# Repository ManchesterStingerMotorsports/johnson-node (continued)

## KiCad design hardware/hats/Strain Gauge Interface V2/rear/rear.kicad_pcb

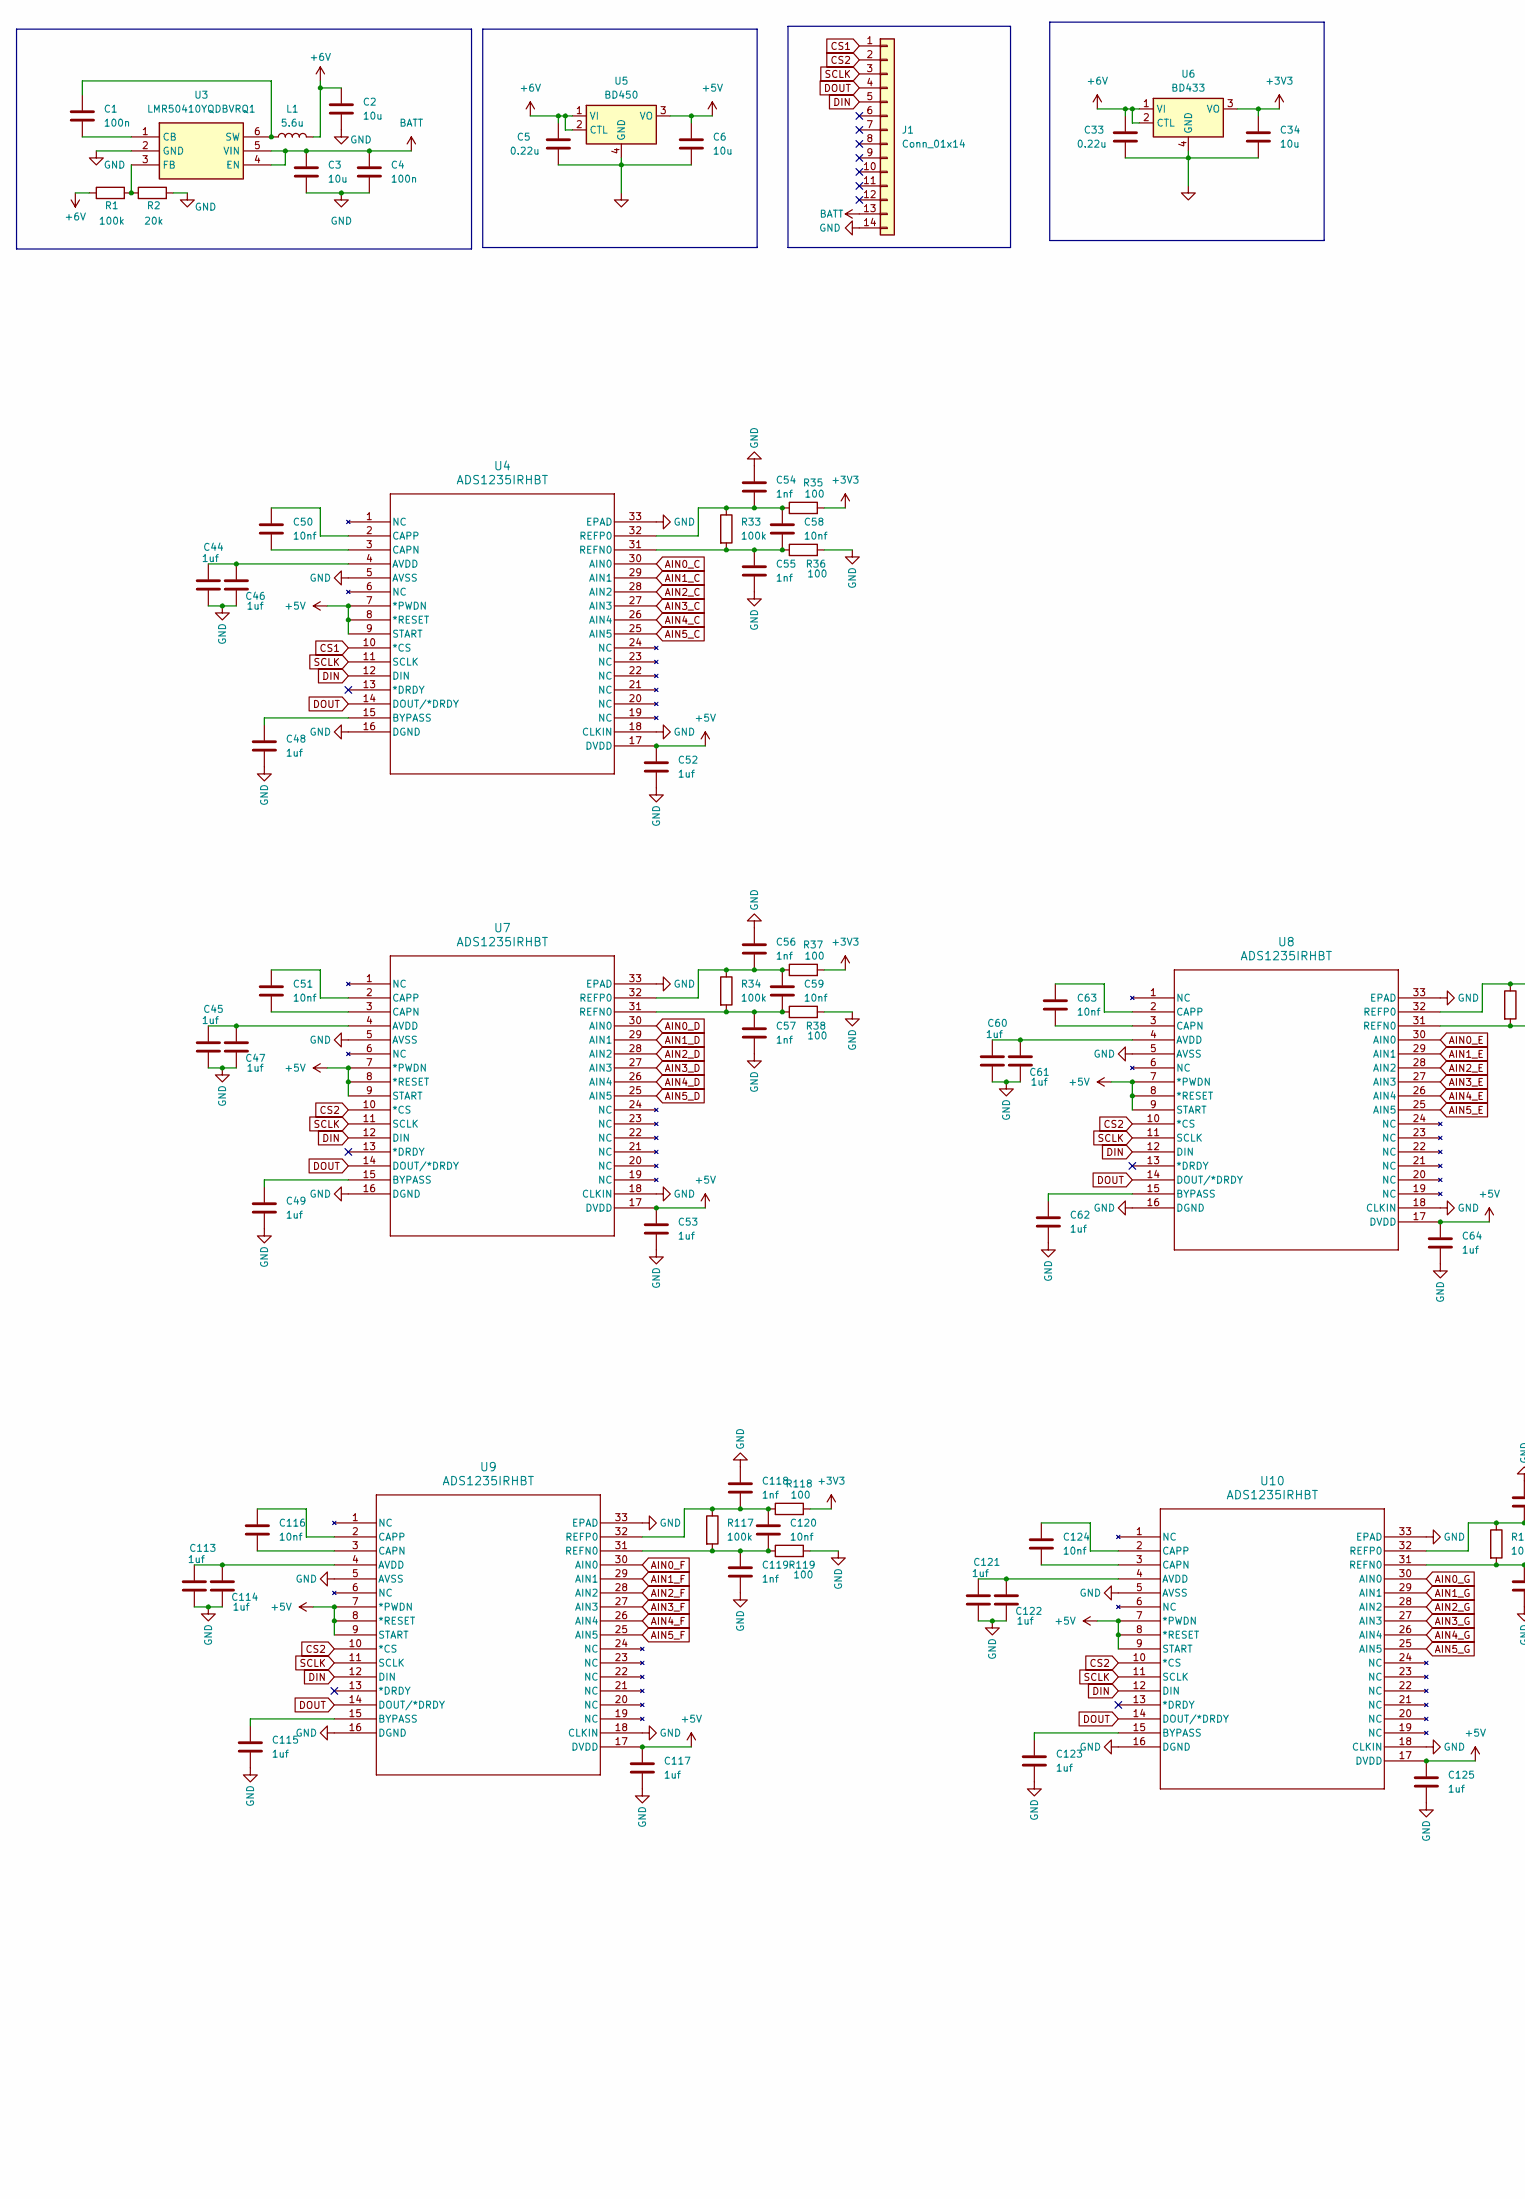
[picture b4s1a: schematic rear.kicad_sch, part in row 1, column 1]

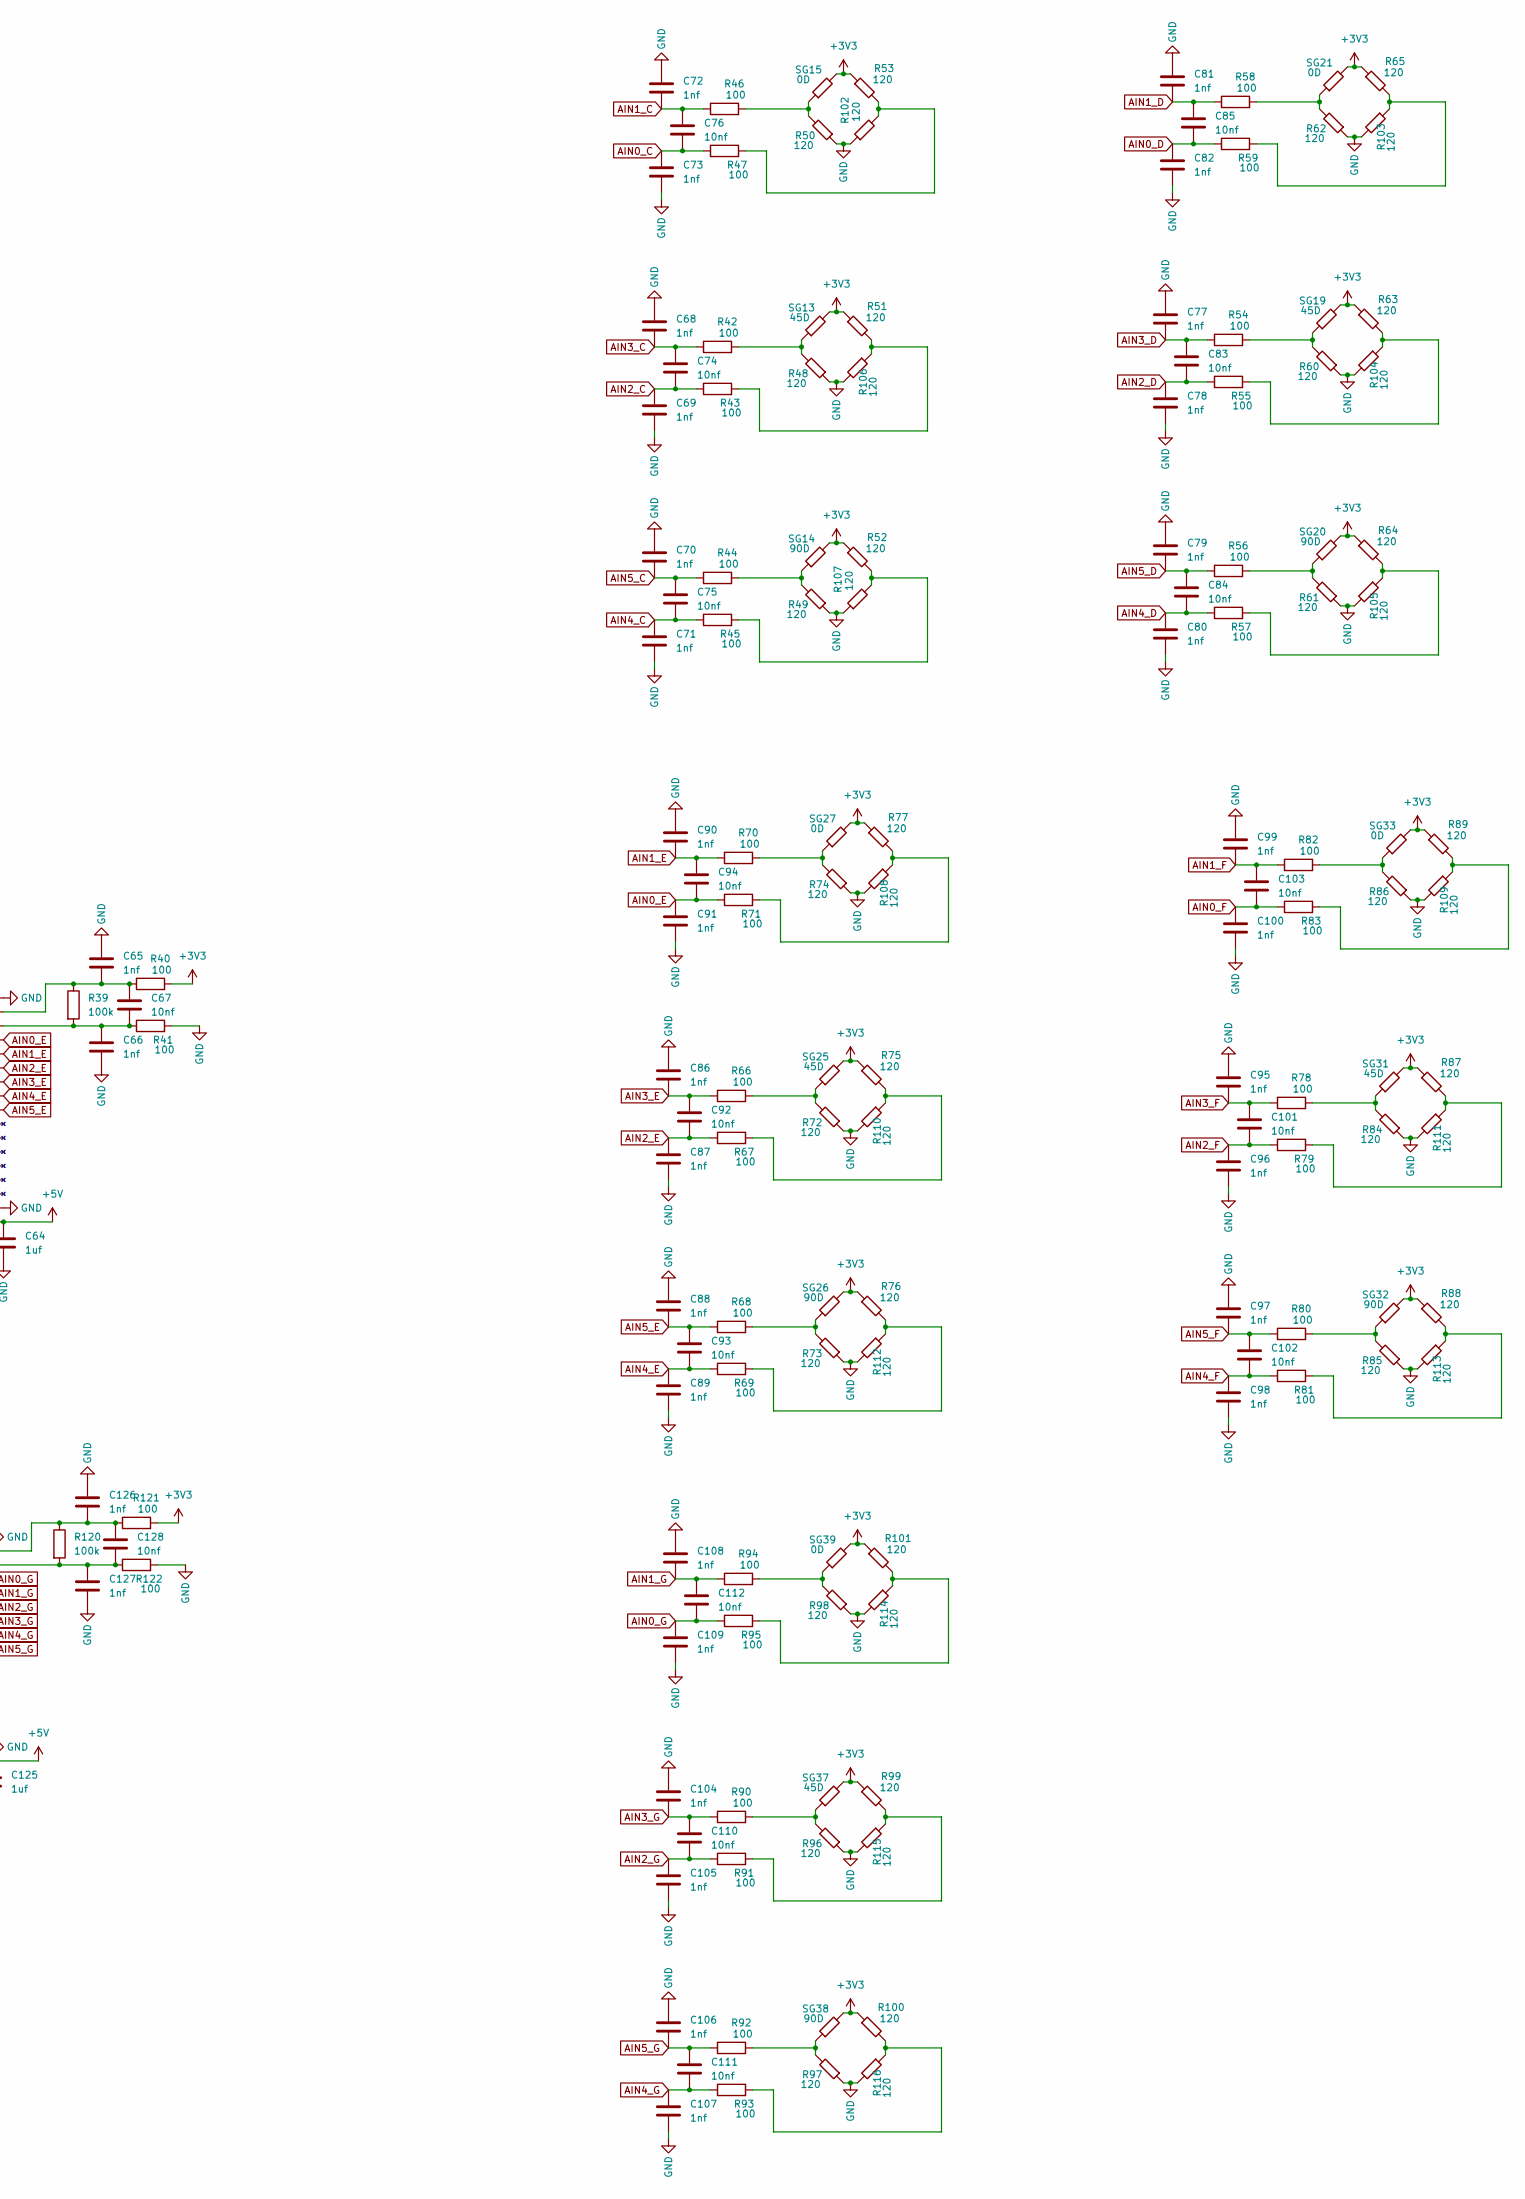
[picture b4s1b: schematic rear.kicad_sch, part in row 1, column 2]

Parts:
C1, C4: 100n; C_0603_1608Metric
C2, C3, C6, C34: 10u; C_0603_1608Metric
C5, C33: 0.22u; C_0603_1608Metric
C44, C45, C46, C47, C48, C49, C52, C53, C60, C61, C62, C64, C113, C114, C115, C117, C121, C122, C123, C125: 1uf; C_0603_1608Metric
C50, C51, C58, C59, C63, C67, C74, C75, C76, C83, C84, C85, C92, C93, C94, C101, C102, C103, C110, C111, C112, C116, C120, C124, C128: 10nf; C_0603_1608Metric
C54, C55, C56, C57, C65, C66, C68, C69, C70, C71, C72, C73, C77, C78, C79, C80, C81, C82, C86, C87, C88, C89, C90, C91, C95, C96, C97, C98, C99, C100, C104, C105, C106, C107, C108, C109, C118, C119, C126, C127: 1nf; C_0603_1608Metric
J1: Conn_01x14; JST_XA_S14B-XASK-1_1x14_P2.50mm_Horizontal
L1: 5.6u; WE-TPC_4828
R1, R33, R34, R39, R117, R120: 100k; R_0603_1608Metric
R2: 20k; R_0603_1608Metric
R35, R36, R37, R38, R40, R41, R42, R43, R44, R45, R46, R47, R54, R55, R56, R57, R58, R59, R66, R67, R68, R69, R70, R71, R78, R79, R80, R81, R82, R83, R90, R91, R92, R93, R94, R95, R118, R119, R121, R122: 100; R_0603_1608Metric
R48, R49, R50, R51, R52, R53, R60, R61, R62, R63, R64, R65, R72, R73, R74, R75, R76, R77, R84, R85, R86, R87, R88, R89, R96, R97, R98, R99, R100, R101, R102, R103, R104, R105, R106, R107, R108, R109, R110, R111, R112, R113, R114, R115, R116: 120; R_0603_1608Metric
SG13, SG19, SG25, SG31, SG37: 45D; JST_XA_S02B-XASK-1_1x02_P2.50mm_Horizontal
SG14, SG20, SG26, SG32, SG38: 90D; JST_XA_S02B-XASK-1_1x02_P2.50mm_Horizontal
SG15, SG21, SG27, SG33, SG39: 0D; JST_XA_S02B-XASK-1_1x02_P2.50mm_Horizontal
U3: LMR50410YQDBVRQ1; SOT95P280X145-6N; Mouser Part Number 595-R50410Y3FQDBVRQ1
U4, U7, U8, U9, U10: ADS1235IRHBT; RHB32_TEX
U5: BD450; Regulator_Linear_SOT-223-4
U6: BD433; Regulator_Linear_SOT-223-4

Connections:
+3V3: C34.1, R35.2, R37.2, R40.2, R51.1, R52.1, R53.1, R63.1, R64.1, R65.1, R75.1, R76.1, R77.1, R87.1, R88.1, R89.1, R99.1, R100.1, R101.1, R118.2, R121.2, SG13.2, SG14.2, SG15.2, SG19.2, SG20.2, SG21.2, SG25.2, SG26.2, SG27.2, SG31.2, SG32.2, SG33.2, SG37.2, SG38.2, SG39.2, U6.3 (VO)
+5V: C6.1, C52.1, C53.1, C64.1, C117.1, C125.1, U4.7 (*PWDN), U4.8 (*RESET), U4.9 (START), U4.17 (DVDD), U5.3 (VO), U7.7 (*PWDN), U7.8 (*RESET), U7.9 (START), U7.17 (DVDD), U8.7 (*PWDN), U8.8 (*RESET), U8.9 (START), U8.17 (DVDD), U9.7 (*PWDN), U9.8 (*RESET), U9.9 (START), U9.17 (DVDD), U10.7 (*PWDN), U10.8 (*RESET), U10.9 (START), U10.17 (DVDD)
+6V: C2.1, C5.1, C33.1, L1.2, R1.1, U5.1 (VI), U5.2 (CTL), U6.1 (VI), U6.2 (CTL)
AIN0_C: C73.1, C76.2, R47.1, U4.30 (AIN0)
AIN0_D: C82.1, C85.2, R59.1, U7.30 (AIN0)
AIN0_E: C91.1, C94.2, R71.1, U8.30 (AIN0)
AIN0_F: C100.1, C103.2, R83.1, U9.30 (AIN0)
AIN0_G: C109.1, C112.2, R95.1, U10.30 (AIN0)
AIN1_C: C72.2, C76.1, R46.1, U4.29 (AIN1)
AIN1_D: C81.2, C85.1, R58.1, U7.29 (AIN1)
AIN1_E: C90.2, C94.1, R70.1, U8.29 (AIN1)
AIN1_F: C99.2, C103.1, R82.1, U9.29 (AIN1)
AIN1_G: C108.2, C112.1, R94.1, U10.29 (AIN1)
AIN2_C: C69.1, C74.2, R43.1, U4.28 (AIN2)
AIN2_D: C78.1, C83.2, R55.1, U7.28 (AIN2)
AIN2_E: C87.1, C92.2, R67.1, U8.28 (AIN2)
AIN2_F: C96.1, C101.2, R79.1, U9.28 (AIN2)
AIN2_G: C105.1, C110.2, R91.1, U10.28 (AIN2)
AIN3_C: C68.2, C74.1, R42.1, U4.27 (AIN3)
AIN3_D: C77.2, C83.1, R54.1, U7.27 (AIN3)
AIN3_E: C86.2, C92.1, R66.1, U8.27 (AIN3)
AIN3_F: C95.2, C101.1, R78.1, U9.27 (AIN3)
AIN3_G: C104.2, C110.1, R90.1, U10.27 (AIN3)
AIN4_C: C71.1, C75.2, R45.1, U4.26 (AIN4)
AIN4_D: C80.1, C84.2, R57.1, U7.26 (AIN4)
AIN4_E: C89.1, C93.2, R69.1, U8.26 (AIN4)
AIN4_F: C98.1, C102.2, R81.1, U9.26 (AIN4)
AIN4_G: C107.1, C111.2, R93.1, U10.26 (AIN4)
AIN5_C: C70.2, C75.1, R44.1, U4.25 (AIN5)
AIN5_D: C79.2, C84.1, R56.1, U7.25 (AIN5)
AIN5_E: C88.2, C93.1, R68.1, U8.25 (AIN5)
AIN5_F: C97.2, C102.1, R80.1, U9.25 (AIN5)
AIN5_G: C106.2, C111.1, R92.1, U10.25 (AIN5)
BATT: C3.1, C4.1, J1.13, U3.4 (EN), U3.5 (VIN)
CS1: J1.1, U4.10 (*CS)
CS2: J1.2, U7.10 (*CS), U8.10 (*CS), U9.10 (*CS), U10.10 (*CS)
DIN: J1.5, U4.12 (DIN), U7.12 (DIN), U8.12 (DIN), U9.12 (DIN), U10.12 (DIN)
DOUT: J1.4, U4.14 (DOUT/*DRDY), U7.14 (DOUT/*DRDY), U8.14 (DOUT/*DRDY), U9.14 (DOUT/*DRDY), U10.14 (DOUT/*DRDY)
GND: C2.2, C3.2, C4.2, C5.2, C6.2, C33.2, C34.2, C44.2, C45.2, C46.2, C47.2, C48.2, C49.2, C52.2, C53.2, C54.1, C55.2, C56.1, C57.2, C60.2, C61.2, C62.2, C64.2, C65.1, C66.2, C68.1, C69.2, C70.1, C71.2, C72.1, C73.2, C77.1, C78.2, C79.1, C80.2, C81.1, C82.2, C86.1, C87.2, C88.1, C89.2, C90.1, C91.2, C95.1, C96.2, C97.1, C98.2, C99.1, C100.2, C104.1, C105.2, C106.1, C107.2, C108.1, C109.2, C113.2, C114.2, C115.2, C117.2, C118.1, C119.2, C121.2, C122.2, C123.2, C125.2, C126.1, C127.2, J1.14, R2.2, R36.2, R38.2, R41.2, R48.1, R49.1, R50.1, R60.1, R61.1, R62.1, R72.1, R73.1, R74.1, R84.1, R85.1, R86.1, R96.1, R97.1, R98.1, R102.1, R103.2, R104.2, R105.2, R106.2, R107.1, R108.2, R109.2, R110.2, R111.2, R112.2, R113.2, R114.2, R115.2, R116.2, R119.2, R122.2, U3.2 (GND), U4.5 (AVSS), U4.16 (DGND), U4.18 (CLKIN), U4.33 (EPAD), U5.4 (GND), U6.4 (GND), U7.5 (AVSS), U7.16 (DGND), U7.18 (CLKIN), U7.33 (EPAD), U8.5 (AVSS), U8.16 (DGND), U8.18 (CLKIN), U8.33 (EPAD), U9.5 (AVSS), U9.16 (DGND), U9.18 (CLKIN), U9.33 (EPAD), U10.5 (AVSS), U10.16 (DGND), U10.18 (CLKIN), U10.33 (EPAD)
unnamed: R42.2, R48.2, SG13.1
unnamed: R44.2, R49.2, SG14.1
unnamed: R46.2, R50.2, SG15.1
unnamed: R54.2, R60.2, SG19.1
unnamed: R56.2, R61.2, SG20.1
unnamed: R58.2, R62.2, SG21.1
unnamed: R66.2, R72.2, SG25.1
unnamed: R68.2, R73.2, SG26.1
unnamed: R70.2, R74.2, SG27.1
unnamed: R78.2, R84.2, SG31.1
unnamed: R80.2, R85.2, SG32.1
unnamed: R82.2, R86.2, SG33.1
unnamed: R90.2, R96.2, SG37.1
unnamed: R92.2, R97.2, SG38.1
unnamed: R94.2, R98.2, SG39.1
unnamed: R93.2, R100.2, R116.1
unnamed: R95.2, R101.2, R114.1
unnamed: R47.2, R53.2, R102.2
unnamed: R59.2, R65.2, R103.1
unnamed: R55.2, R63.2, R104.1
unnamed: R57.2, R64.2, R105.1
unnamed: R43.2, R51.2, R106.1
unnamed: R45.2, R52.2, R107.2
unnamed: R71.2, R77.2, R108.1
unnamed: R83.2, R89.2, R109.1
unnamed: R67.2, R75.2, R110.1
unnamed: R79.2, R87.2, R111.1
unnamed: R69.2, R76.2, R112.1
unnamed: R81.2, R88.2, R113.1
unnamed: R91.2, R99.2, R115.1
unnamed: C1.2, U3.1 (CB)
unnamed: R1.2, R2.1, U3.3 (FB)
unnamed: C1.1, L1.1, U3.6 (SW)
unnamed: C44.1, C46.1, U4.4 (AVDD)
unnamed: C48.1, U4.15 (BYPASS)
unnamed: C50.2, U4.3 (CAPN)
unnamed: C50.1, U4.2 (CAPP)
unnamed: C55.1, C58.2, R33.2, R36.1, U4.31 (REFN0)
unnamed: C54.2, C58.1, R33.1, R35.1, U4.32 (REFP0)
unnamed: C45.1, C47.1, U7.4 (AVDD)
unnamed: C49.1, U7.15 (BYPASS)
unnamed: C51.2, U7.3 (CAPN)
unnamed: C51.1, U7.2 (CAPP)
unnamed: C57.1, C59.2, R34.2, R38.1, U7.31 (REFN0)
unnamed: C56.2, C59.1, R34.1, R37.1, U7.32 (REFP0)
unnamed: C60.1, C61.1, U8.4 (AVDD)
unnamed: C62.1, U8.15 (BYPASS)
unnamed: C63.2, U8.3 (CAPN)
unnamed: C63.1, U8.2 (CAPP)
unnamed: C66.1, C67.2, R39.2, R41.1, U8.31 (REFN0)
unnamed: C65.2, C67.1, R39.1, R40.1, U8.32 (REFP0)
unnamed: C113.1, C114.1, U9.4 (AVDD)
unnamed: C115.1, U9.15 (BYPASS)
unnamed: C116.2, U9.3 (CAPN)
unnamed: C116.1, U9.2 (CAPP)
unnamed: C119.1, C120.2, R117.2, R119.1, U9.31 (REFN0)
unnamed: C118.2, C120.1, R117.1, R118.1, U9.32 (REFP0)
unnamed: C121.1, C122.1, U10.4 (AVDD)
unnamed: C123.1, U10.15 (BYPASS)
unnamed: C124.2, U10.3 (CAPN)
unnamed: C124.1, U10.2 (CAPP)
unnamed: C127.1, C128.2, R120.2, R122.1, U10.31 (REFN0)
unnamed: C126.2, C128.1, R120.1, R121.1, U10.32 (REFP0)
SCLK: J1.3, U4.11 (SCLK), U7.11 (SCLK), U8.11 (SCLK), U9.11 (SCLK), U10.11 (SCLK)

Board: 2 copper layers, 210 parts (0 on the bottom side), 103 nets, no tracks yet.

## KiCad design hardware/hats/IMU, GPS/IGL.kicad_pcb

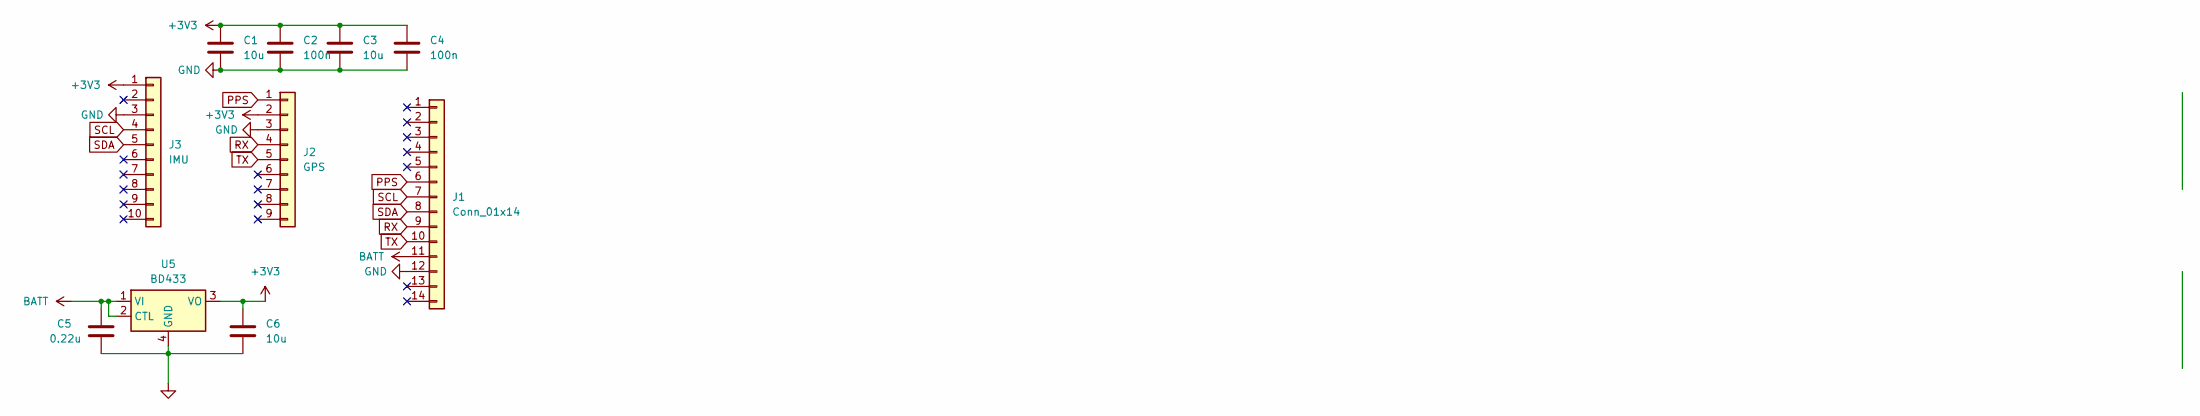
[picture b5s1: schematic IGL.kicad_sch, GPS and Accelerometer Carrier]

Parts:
C1, C3, C6: 10u; C_0603_1608Metric
C2, C4: 100n; C_0603_1608Metric
C5: 0.22u; C_0603_1608Metric
J1: Conn_01x14; JST_XA_S14B-XASK-1_1x14_P2.50mm_Horizontal
J2: GPS
J3: IMU
U5: BD433; Regulator_Linear_SOT-223-4

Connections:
+3V3: C1.1, C2.1, C3.1, C4.1, C6.1, J2.2, J3.1, U5.3 (VO)
BATT: C5.1, J1.11, U5.1 (VI), U5.2 (CTL)
GND: C1.2, C2.2, C3.2, C4.2, C5.2, C6.2, J1.12, J2.3, J3.3, U5.4 (GND)
PPS: J1.6, J2.1
RX: J1.9, J2.4
SCL: J1.7, J3.4
SDA: J1.8, J3.5
TX: J1.10, J2.5

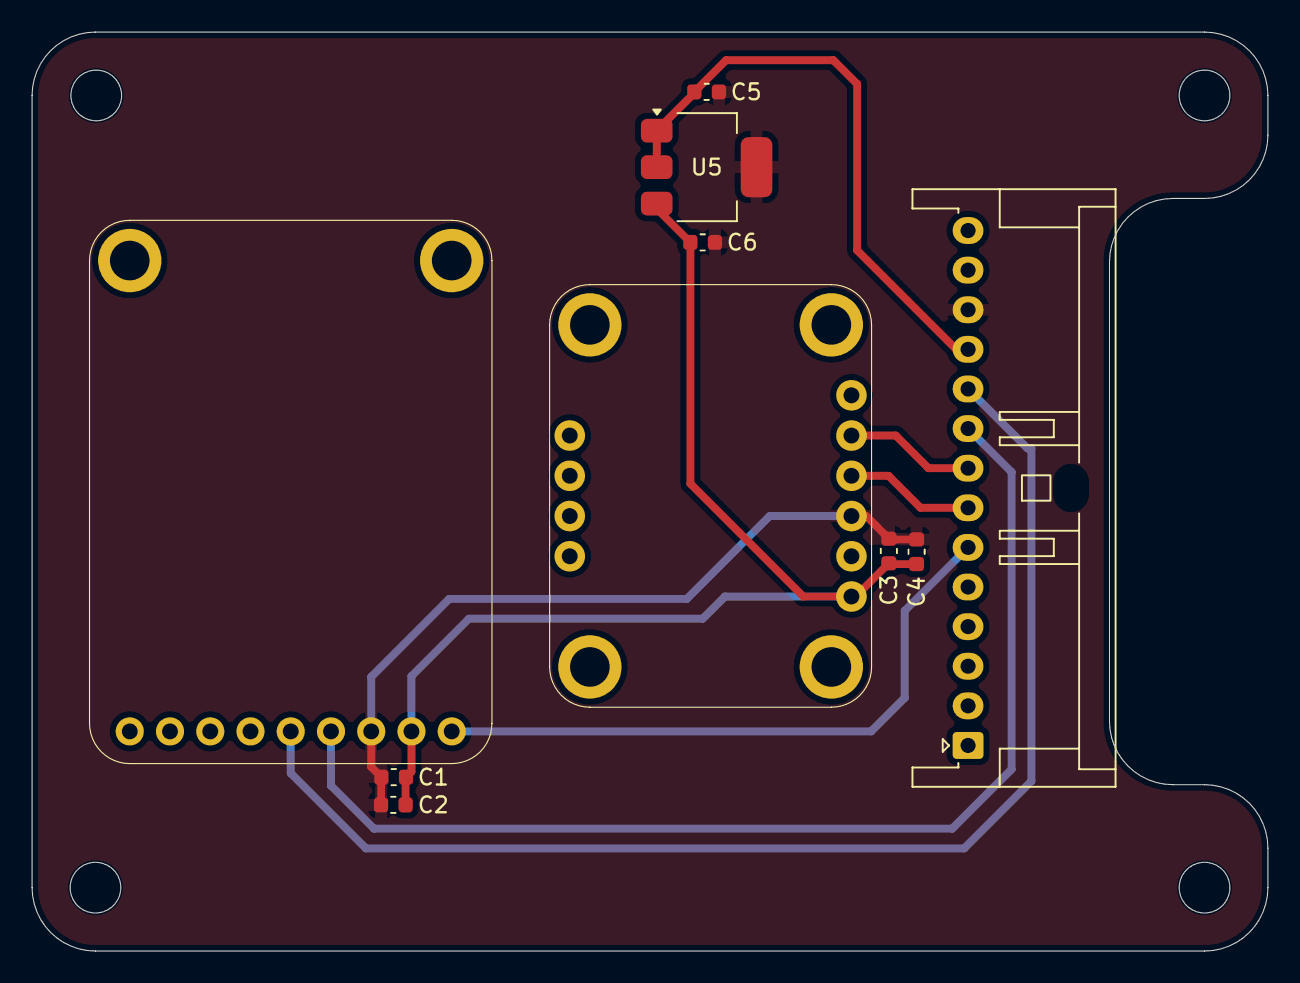
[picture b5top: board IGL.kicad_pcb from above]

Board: 2 copper layers, 78.0 x 58.0 mm, 10 parts (0 on the bottom side), 8 nets.

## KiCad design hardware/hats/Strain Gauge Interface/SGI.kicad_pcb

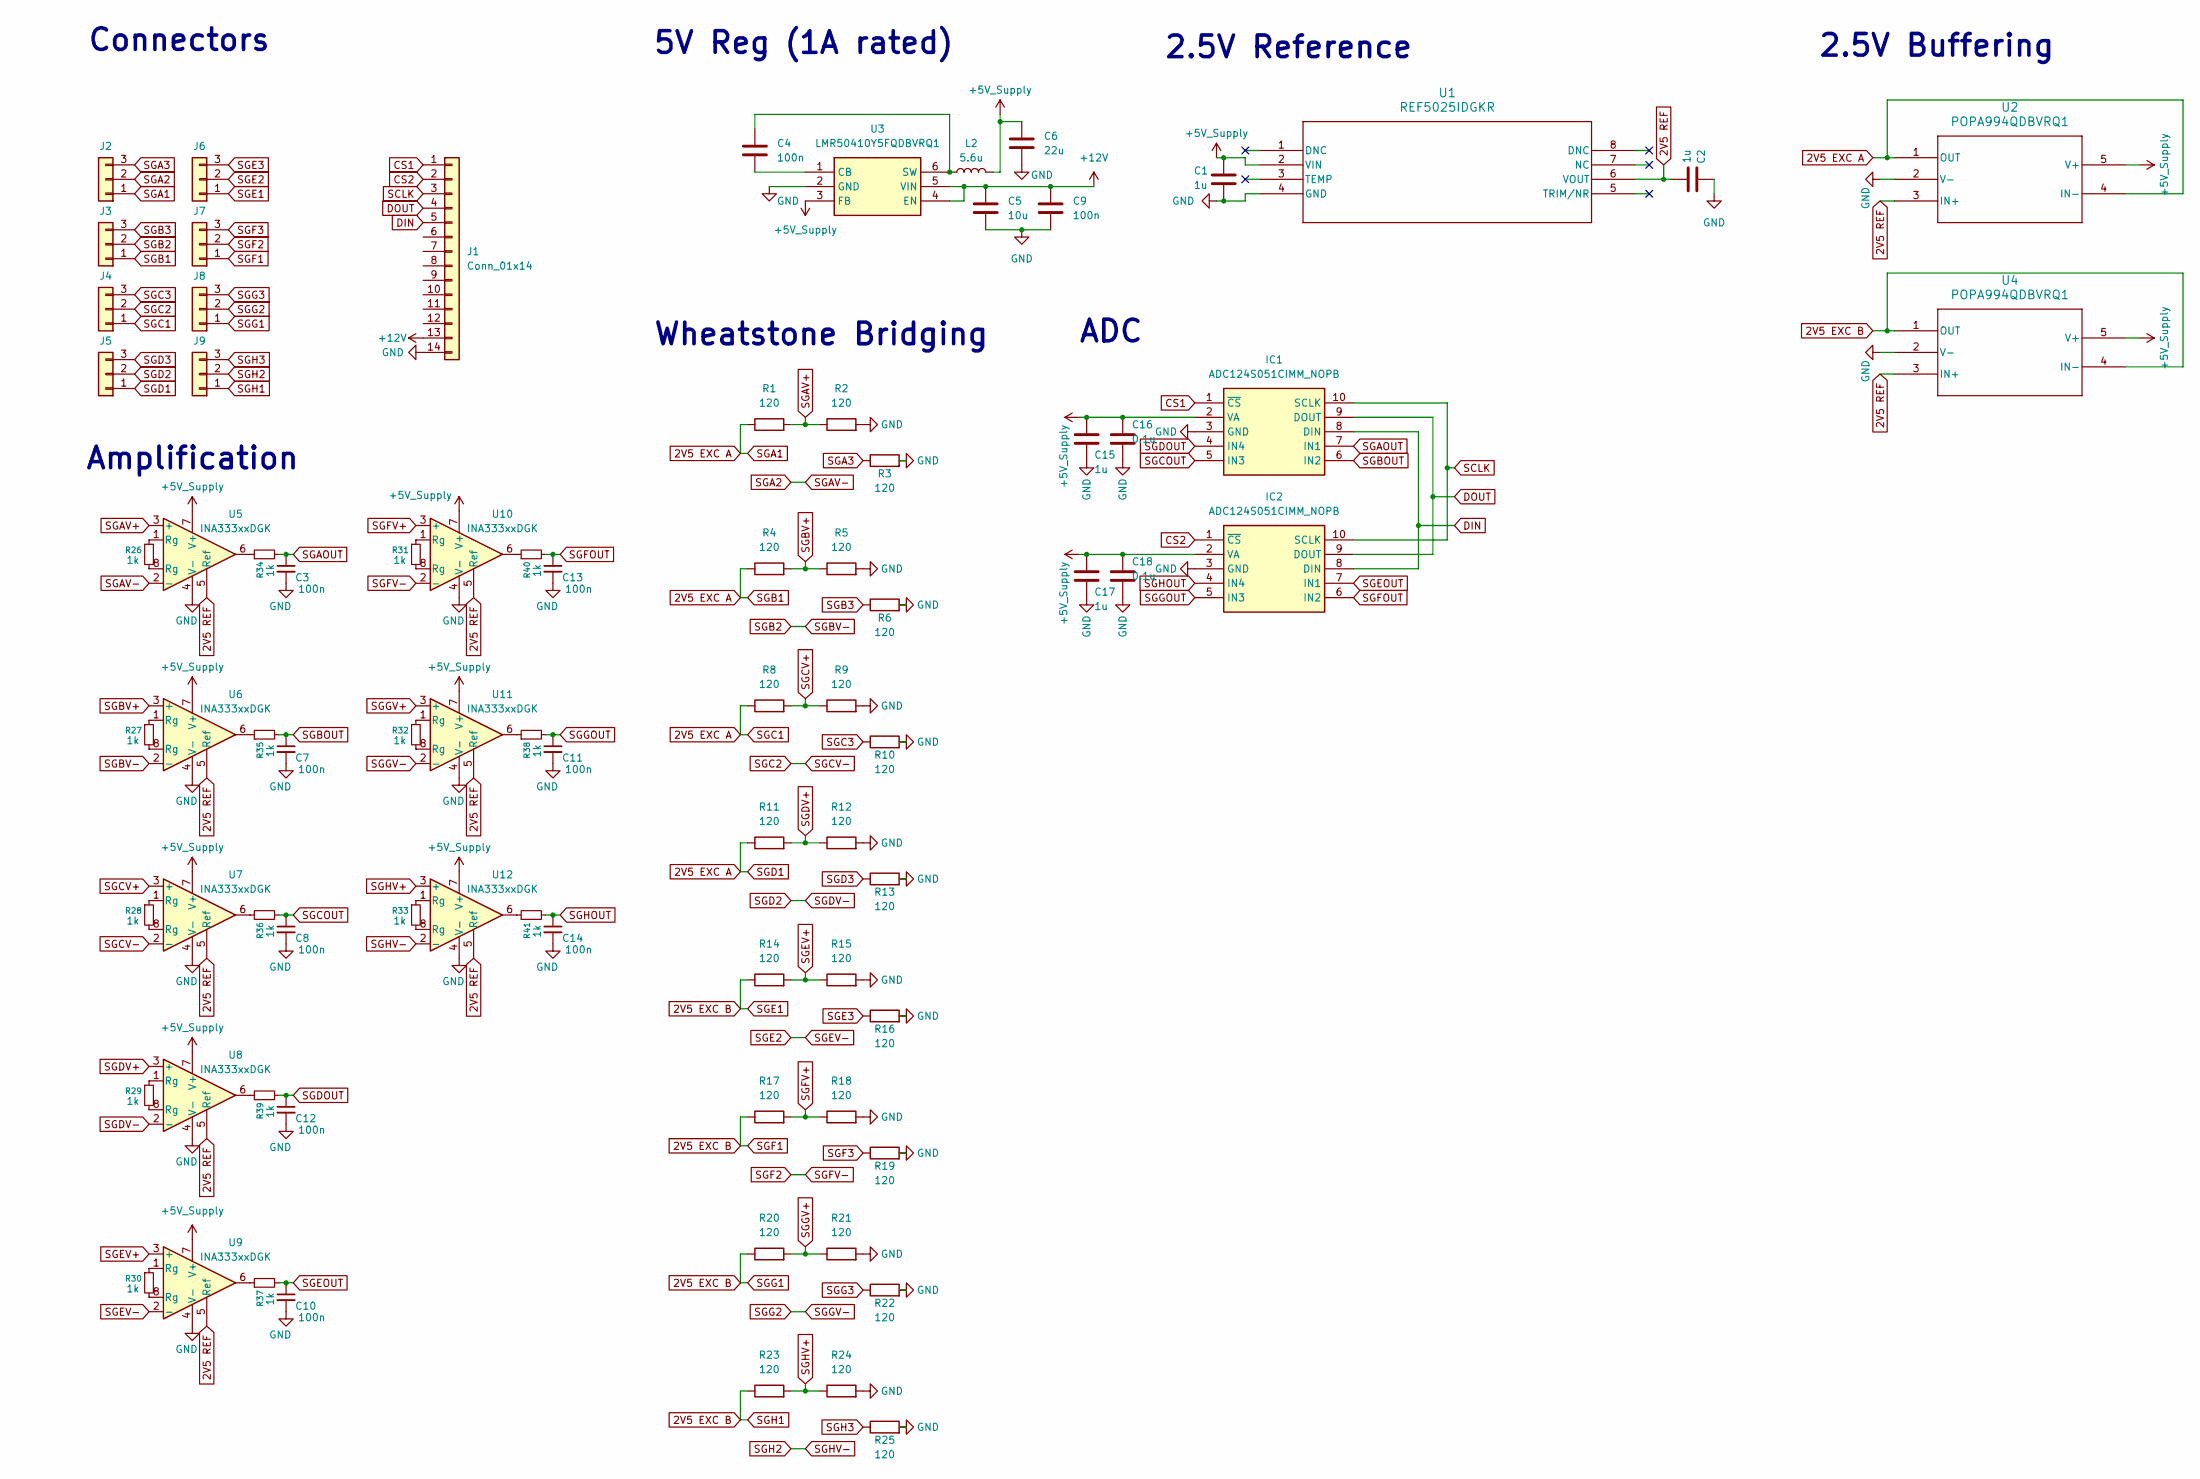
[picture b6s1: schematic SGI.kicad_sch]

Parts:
C1, C2, C15, C17: 1u; C_0603_1608Metric
C3, C4, C7, C8, C9, C10, C11, C12, C13, C14: 100n; C_0603_1608Metric
C5: 10u; C_0603_1608Metric
C6: 22u; C_0603_1608Metric
C16, C18: 0.1u; C_0603_1608Metric
IC1, IC2: ADC124S051CIMM_NOPB; SOP50P490X110-10N; Mouser Part Number 926-AD124S051CIMMNPB
J1: Conn_01x14; JST_XA_S14B-XASK-1_1x14_P2.50mm_Horizontal
J2, J3, J4, J5, J6, J7, J8, J9: S03B-XASK-1; JST_XA_S03B-XASK-1_1x03_P2.50mm_Horizontal
L2: 5.6u; WE-TPC_4828
R1, R2, R3, R4, R5, R6, R8, R9, R10, R11, R12, R13, R14, R15, R16, R17, R18, R19, R20, R21, R22, R23, R24, R25: 120; R_0603_1608Metric
R26, R27, R28, R29, R30, R31, R32, R33, R34, R35, R36, R37, R38, R39, R40, R41: 1k; R_0603_1608Metric
U1: REF5025IDGKR; DGK8
U2, U4: POPA994QDBVRQ1; DBV0005A_TEX
U3: LMR50410Y5FQDBVRQ1; Regulator_Switching_SOT-23-6; Mouser Part Number 595-R50410Y3FQDBVRQ1
U5, U6, U7, U8, U9, U10, U11, U12: INA333xxDGK; VSSOP-8_3x3mm_P0.65mm

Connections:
2V5 EXC A: J2.1, J3.1, J4.1, J5.1, R1.1, R4.1, R8.1, R11.1, U2.1 (OUT), U2.4 (IN-)
2V5 EXC B: J6.1, J7.1, J8.1, J9.1, R14.1, R17.1, R20.1, R23.1, U4.1 (OUT), U4.4 (IN-)
2V5 REF: C2.1, U1.6 (VOUT), U2.3 (IN+), U4.3 (IN+), U5.5 (Ref), U6.5 (Ref), U7.5 (Ref), U8.5 (Ref), U9.5 (Ref), U10.5 (Ref), U11.5 (Ref), U12.5 (Ref)
+5V_Supply: C1.2, C6.1, C15.1, C16.1, C17.1, C18.1, IC1.2 (VA), IC2.2 (VA), L2.2, U1.2 (VIN), U2.5 (V+), U3.3 (FB), U4.5 (V+), U5.7 (V+), U6.7 (V+), U7.7 (V+), U8.7 (V+), U9.7 (V+), U10.7 (V+), U11.7 (V+), U12.7 (V+)
+12V: C5.1, C9.1, J1.13, U3.4 (EN), U3.5 (VIN)
CS1: IC1.1 (~CS), J1.1
CS2: IC2.1 (~CS), J1.2
DIN: IC1.8 (DIN), IC2.8 (DIN), J1.5
DOUT: IC1.9 (DOUT), IC2.9 (DOUT), J1.4
GND: C1.1, C2.2, C3.2, C5.2, C6.2, C7.2, C8.2, C9.2, C10.2, C11.2, C12.2, C13.2, C14.2, C15.2, C16.2, C17.2, C18.2, IC1.3 (GND), IC2.3 (GND), J1.14, R2.2, R3.2, R5.2, R6.2, R9.2, R10.2, R12.2, R13.2, R15.2, R16.2, R18.2, R19.2, R21.2, R22.2, R24.2, R25.2, U1.4 (GND), U2.2 (V-), U3.2 (GND), U4.2 (V-), U5.4 (V-), U6.4 (V-), U7.4 (V-), U8.4 (V-), U9.4 (V-), U10.4 (V-), U11.4 (V-), U12.4 (V-)
unnamed: R26.1, U5.1 (Rg)
unnamed: R26.2, U5.8 (Rg)
unnamed: R27.1, U6.1 (Rg)
unnamed: R27.2, U6.8 (Rg)
unnamed: R28.1, U7.1 (Rg)
unnamed: R28.2, U7.8 (Rg)
unnamed: R29.1, U8.1 (Rg)
unnamed: R29.2, U8.8 (Rg)
unnamed: R30.1, U9.1 (Rg)
unnamed: R30.2, U9.8 (Rg)
unnamed: R31.1, U10.1 (Rg)
unnamed: R31.2, U10.8 (Rg)
unnamed: R32.1, U11.1 (Rg)
unnamed: R32.2, U11.8 (Rg)
unnamed: R33.1, U12.1 (Rg)
unnamed: R33.2, U12.8 (Rg)
unnamed: R34.1, U5.6
unnamed: R35.1, U6.6
unnamed: R36.1, U7.6
unnamed: R37.1, U9.6
unnamed: R38.1, U11.6
unnamed: R39.1, U8.6
unnamed: R40.1, U10.6
unnamed: R41.1, U12.6
unnamed: C4.2, U3.1 (CB)
unnamed: C4.1, L2.1, U3.6 (SW)
SCLK: IC1.10 (SCLK), IC2.10 (SCLK), J1.3
SGA2: J2.2, U5.2 (-)
SGA3: J2.3, R3.1
SGAOUT: C3.1, IC1.7 (IN1), R34.2
SGAV+: R1.2, R2.1, U5.3 (+)
SGB2: J3.2, U6.2 (-)
SGB3: J3.3, R6.1
SGBOUT: C7.1, IC1.6 (IN2), R35.2
SGBV+: R4.2, R5.1, U6.3 (+)
SGC2: J4.2, U7.2 (-)
SGC3: J4.3, R10.1
SGCOUT: C8.1, IC1.5 (IN3), R36.2
SGCV+: R8.2, R9.1, U7.3 (+)
SGD2: J5.2, U8.2 (-)
SGD3: J5.3, R13.1
SGDOUT: C12.1, IC1.4 (IN4), R39.2
SGDV+: R11.2, R12.1, U8.3 (+)
SGE2: J6.2, U9.2 (-)
SGE3: J6.3, R16.1
SGEOUT: C10.1, IC2.7 (IN1), R37.2
SGEV+: R14.2, R15.1, U9.3 (+)
SGF2: J7.2, U10.2 (-)
SGF3: J7.3, R19.1
SGFOUT: C13.1, IC2.6 (IN2), R40.2
SGFV+: R17.2, R18.1, U10.3 (+)
SGG2: J8.2, U11.2 (-)
SGG3: J8.3, R22.1
SGGOUT: C11.1, IC2.5 (IN3), R38.2
SGGV+: R20.2, R21.1, U11.3 (+)
SGH2: J9.2, U12.2 (-)
SGH3: J9.3, R25.1
SGHOUT: C14.1, IC2.4 (IN4), R41.2
SGHV+: R23.2, R24.1, U12.3 (+)

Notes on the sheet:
(1A rated)
Wheatstone Bridging
Amplification
Connectors
ADC
2.5V Buffering
5V Reg
2.5V Reference

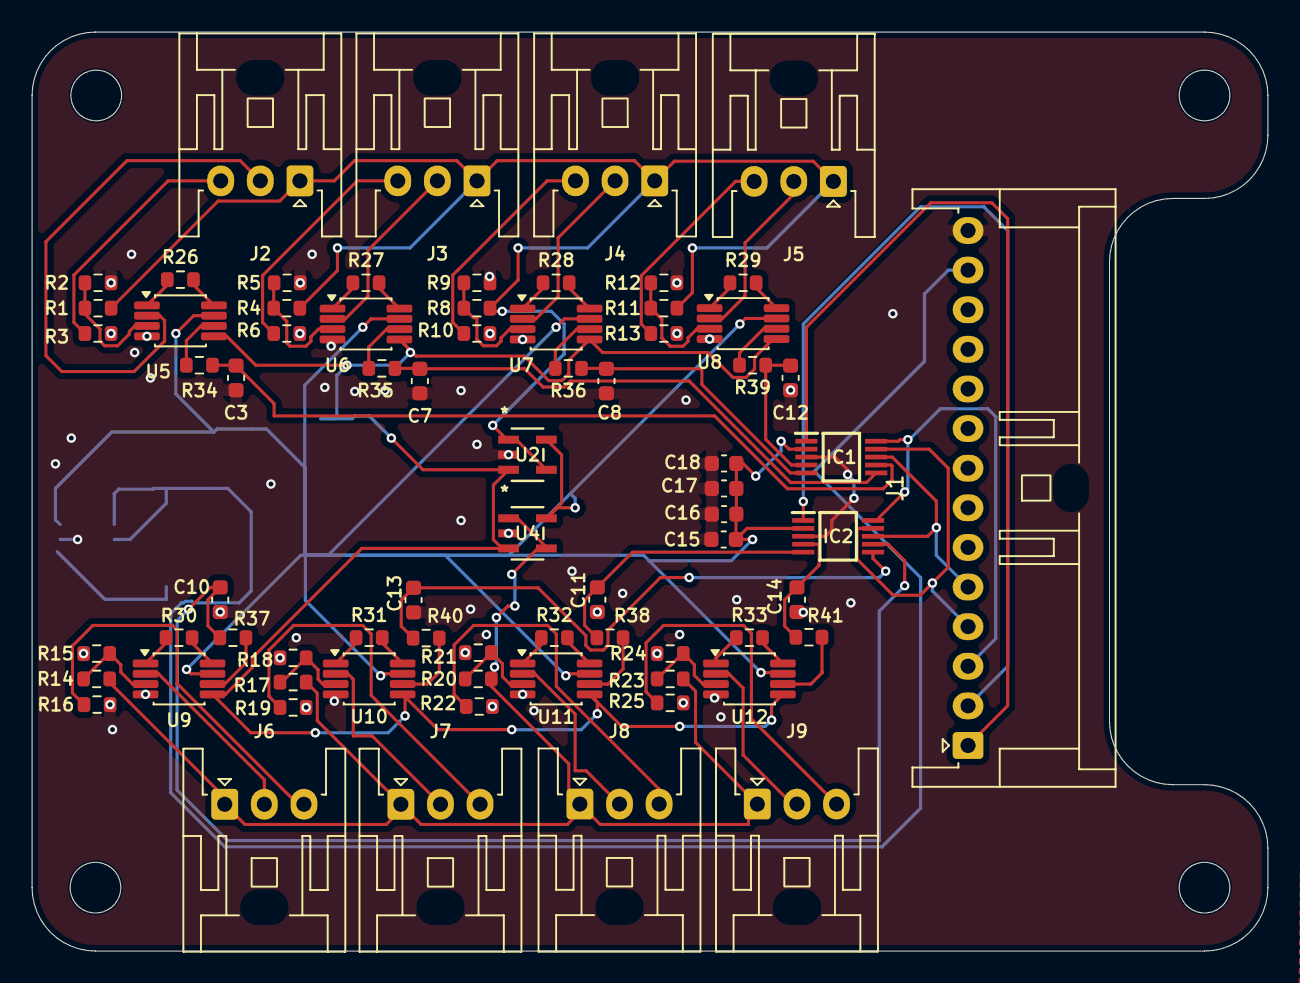
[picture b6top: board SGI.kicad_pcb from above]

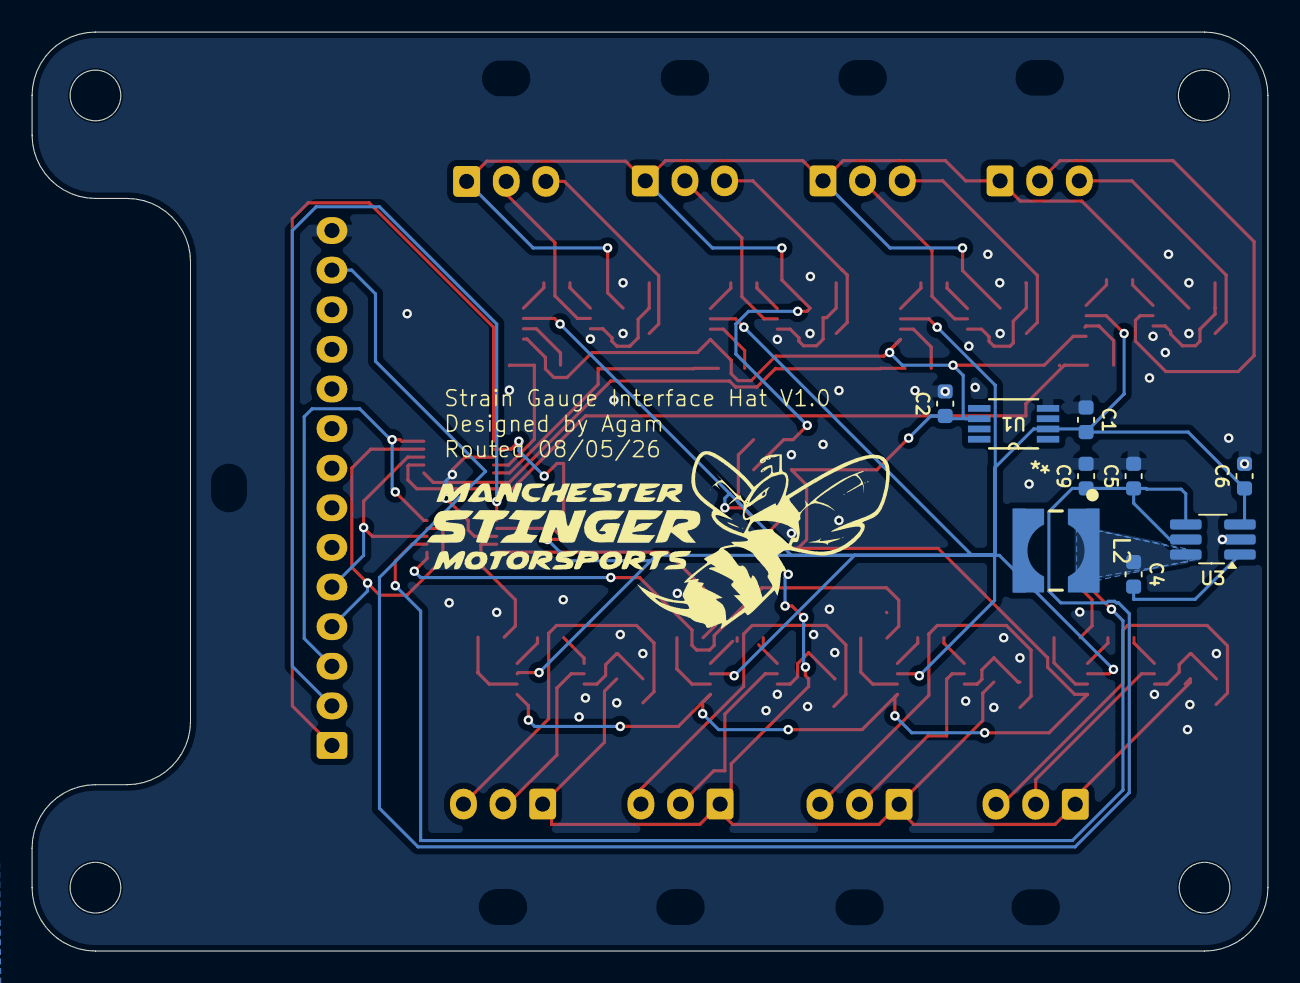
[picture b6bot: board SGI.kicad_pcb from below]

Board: 2 copper layers, 78.0 x 58.0 mm, 82 parts (9 on the bottom side), 69 nets.
